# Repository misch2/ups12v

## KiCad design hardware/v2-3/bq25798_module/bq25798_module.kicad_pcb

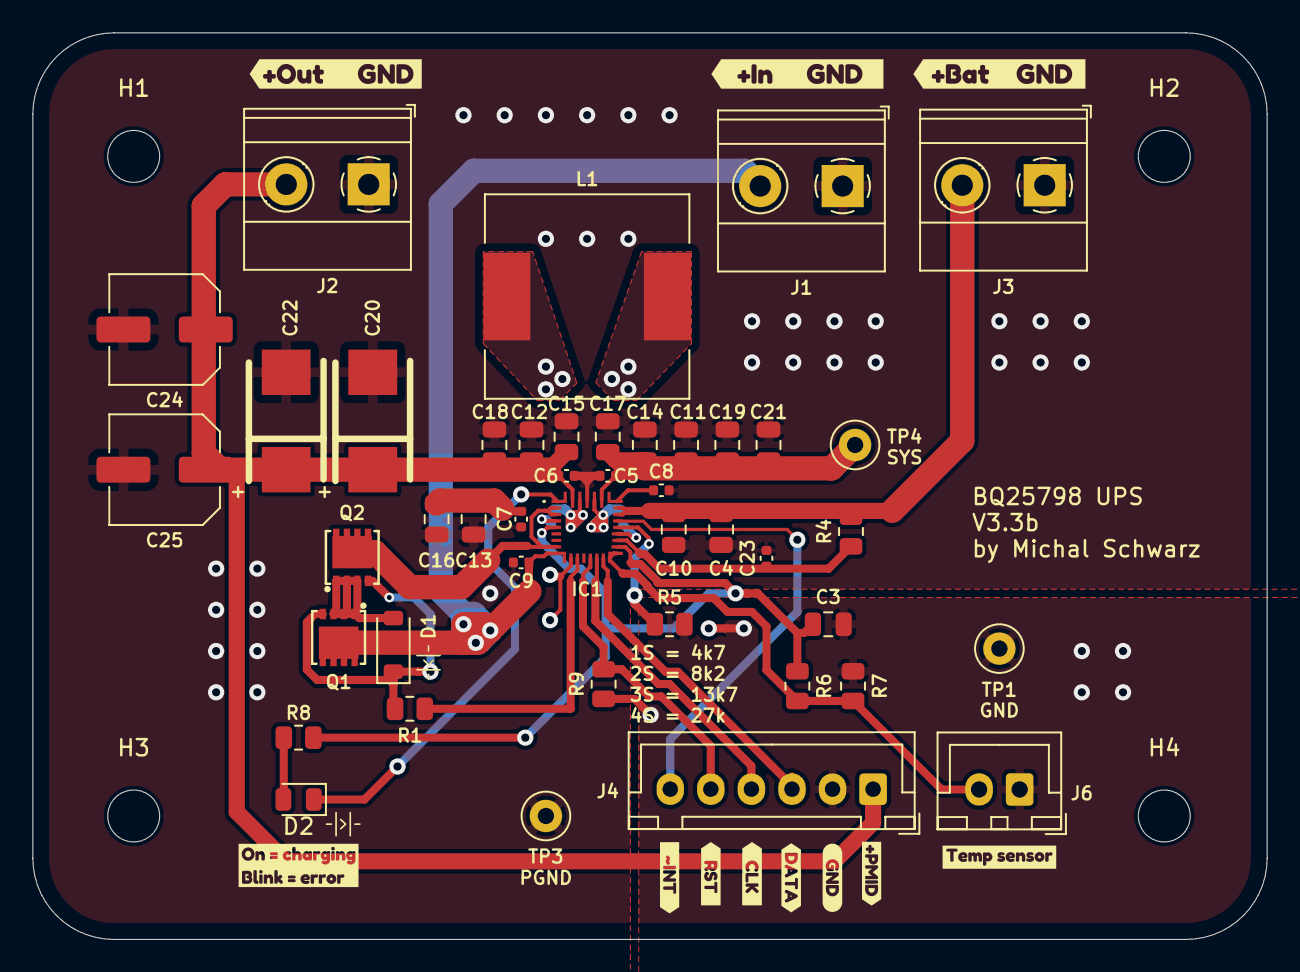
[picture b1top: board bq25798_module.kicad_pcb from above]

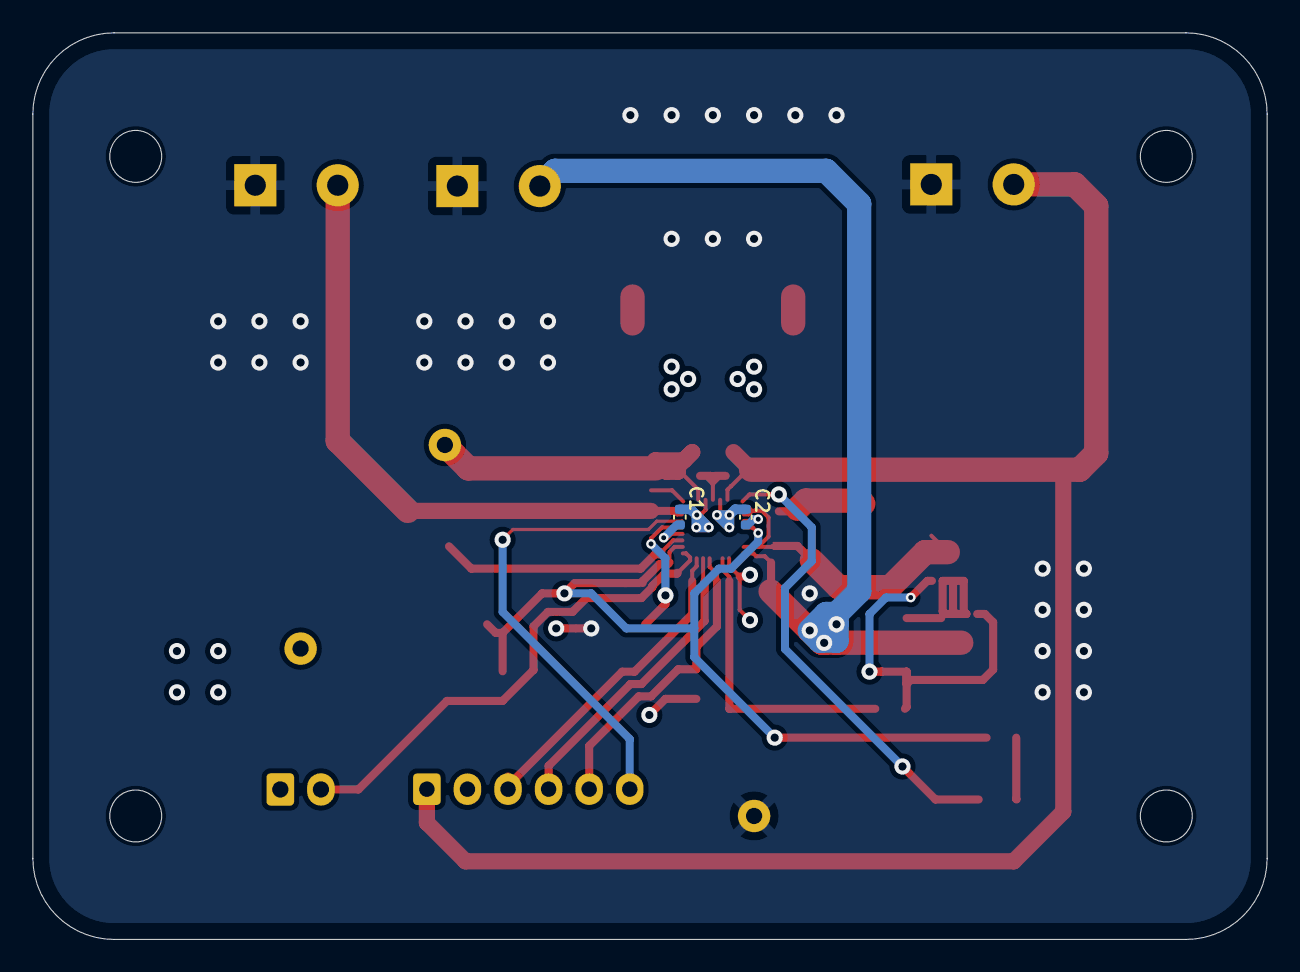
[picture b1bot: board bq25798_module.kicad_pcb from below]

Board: 4 copper layers, 76.0 x 55.9 mm, 64 parts (2 on the bottom side), 28 nets.

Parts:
C1, C2, C23: 47n 25V; C_0402_1005Metric
C3: 4.7u 10V; C_0805_2012Metric
C4, C10, C11, C12, C13, C14, C15, C16, C17, C18, C19, C21: 10u 25V; C_0805_2012Metric
C5, C6, C7, C9: 100n 25V; C_0402_1005Metric
C8: 1nF, 50V; C_0402_1005Metric
C20, C22: 47u POSCAP; CASE-D_7343
C24, C25: 47u low ESR; C_Elec_6.3x5.8
D1: 12V; D_SOD-123
D2: LED; LED_0805_2012Metric
H1, H2, H3, H4: MountingHole; MountingHole_3.2mm_M3
IC1: BQ25798RQMR; BQ25798RQMR_smaller_protected_area
J1: Input 12V DC; TerminalBlock_Phoenix_MKDS-1,5-2-5.08_1x02_P5.08mm_Horizont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
J2: Output 12V DC; TerminalBlock_Phoenix_MKDS-1,5-2-5.08_1x02_P5.08mm_Horizont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
J3: Battery; TerminalBlock_Phoenix_MKDS-1,5-2-5.08_1x02_P5.08mm_Horizont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
J4: Conn_01x06_Pin; JST_XH_B6B-XH-A_1x06_P2.50mm_Vertical
J6: NTC temp sensor; JST_XH_B2B-XH-A_1x02_P2.50mm_Vertical
L1: 2.2uH; L_12x12mm_H6mm
NT1, NT2, NT4: NetTie-2_SMD_Pad0.5mm
Q1, Q2: AON7528; DFN-8_L3.3-W3.3-P0.65-BL-3
R1: 270R; R_0805_2012Metric
R4: 100R; R_0805_2012Metric
R5: 27k 1-2%; R_0805_2012Metric
R6: 5k6; R_0805_2012Metric
R7: 33k; R_0805_2012Metric
R8: 2k2; R_0805_2012Metric
R9: 10k; R_0805_2012Metric
TP1: GND; TestPoint_Loop_D1.80mm_Drill1.0mm_Beaded
TP3: PGND; TestPoint_Loop_D1.80mm_Drill1.0mm_Beaded
TP4: SYS; TestPoint_Loop_D1.80mm_Drill1.0mm_Beaded
kibuzzard-680F50CE: G***; kibuzzard-680F50CE
kibuzzard-680F50E1: G***; kibuzzard-680F50E1
kibuzzard-680F50F5: G***; kibuzzard-680F50F5
kibuzzard-680F5553: G***; kibuzzard-680F5553
kibuzzard-680FCC32: G***; kibuzzard-680FCC32
kibuzzard-6810EFE9: G***; kibuzzard-6810EFE9
kibuzzard-6810F0BF: G***; kibuzzard-6810F0BF
kibuzzard-6810F0CD: G***; kibuzzard-6810F0CD
kibuzzard-6810F0D5: G***; kibuzzard-6810F0D5
kibuzzard-6810F062: G***; kibuzzard-6810F062
kibuzzard-68585403: G***; kibuzzard-68585403

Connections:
/I2C_SCL: IC1.14 (SCL), J4.4
/I2C_SDA: IC1.15 (SDA), J4.3
/~INT: IC1.21 (~INT), J4.6
/~RST: IC1.13 (~CE), J4.5, R9.2
BATTERY: C4.1, C10.1, IC1.22 (BAT_1), IC1.23 (BAT_2), J3.2, R4.2
BTST1: C2.1, IC1.4 (BTST1)
BTST2: C1.2, IC1.19 (BTST2)
GND: C3.2, IC1.10 (ACDRV2), J4.2, J6.1, NT1.1, R5.2, R7.1, R9.1, TP1.1
ILIM_HIZ: IC1.17 (ILIM_HIZ), NT2.1
unnamed: D1.2 (A), Q1.1 (S), Q1.2 (S), Q1.3 (S), Q2.1 (S), Q2.2 (S), Q2.3 (S)
unnamed: D1.1 (K), Q1.4 (G), Q2.4 (G), R1.2
unnamed: D2.2 (A), R8.2
unnamed: IC1.11 (ACDRV1), R1.1
unnamed: C23.1, IC1.18 (BATP), R4.1
unnamed: IC1.20 (PROG), R5.1
unnamed: IC1.2 (VBUS_1), IC1.3 (VBUS_2), IC1.8 (VAC2), NT4.1
unnamed: NT4.2, Q2.5 (D), Q2.6 (D), Q2.7 (D), Q2.8 (D), Q2.9 (D)
PGND: C4.2, C5.2, C6.2, C7.2, C8.2, C9.2, C10.2, C11.2, C12.2, C13.2, C14.2, C15.2, C16.2, C17.2, C18.2, C19.2, C20.2, C21.2, C22.2, C23.2, C24.2, C25.2, IC1.27 (GND), J1.1, J2.1, J3.1, NT1.2, TP3.1
PMID: C6.1, C12.1, C15.1, C18.1, C20.1, C22.1, C24.1, C25.1, IC1.29 (PMID), J2.2, J4.1
REGN: C3.1, IC1.5 (REGN), NT2.2, R6.1, R8.1
SDRV: C8.1, IC1.24 (SDRV_1), IC1.33 (SDRV_2)
STAT: D2.1 (K), IC1.1 (STAT_1), IC1.30 (STAT_2)
SW1: C2.2, IC1.28 (SW1), L1.2
SW2: C1.1, IC1.26 (SW2), L1.1
SYS: C5.1, C11.1, C14.1, C17.1, C19.1, C21.1, IC1.25 (SYS), TP4.1
TS: IC1.16 (TS_1), IC1.32 (TS_2), J6.2, R6.2, R7.2
VBUS: C7.1, C13.1, C16.1
VIN1: C9.1, IC1.9 (VAC1_1), IC1.31 (VAC1_2), J1.2, Q1.5 (D), Q1.6 (D), Q1.7 (D), Q1.8 (D), Q1.9 (D)

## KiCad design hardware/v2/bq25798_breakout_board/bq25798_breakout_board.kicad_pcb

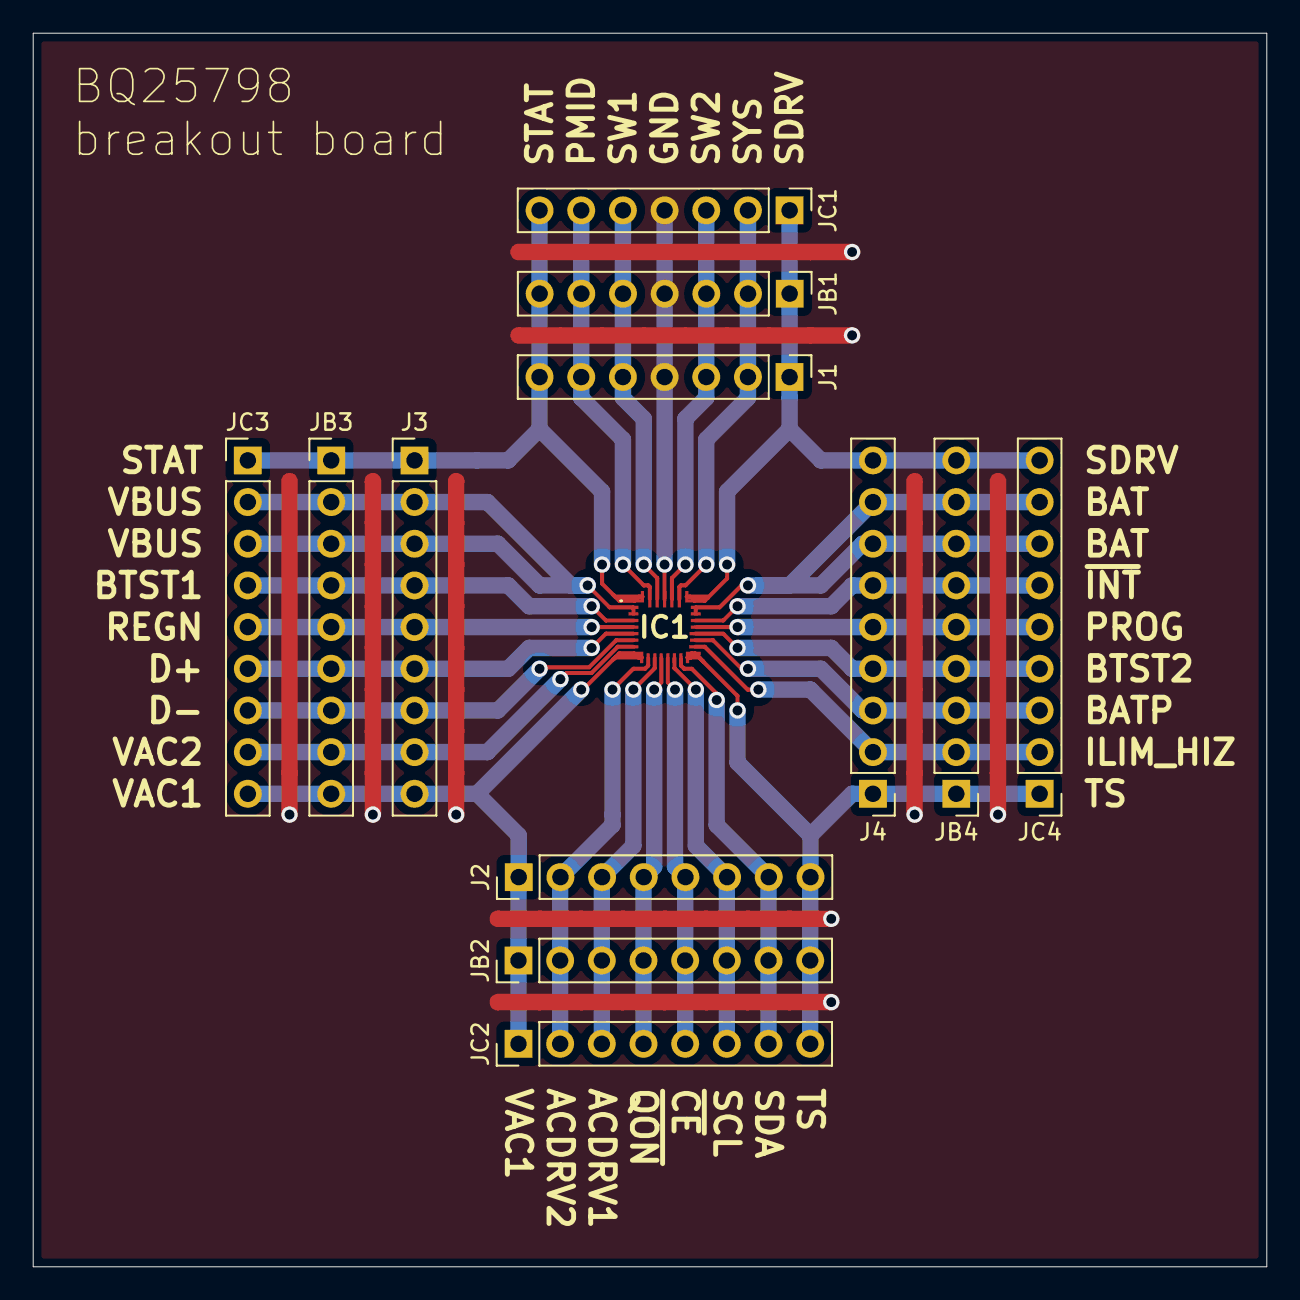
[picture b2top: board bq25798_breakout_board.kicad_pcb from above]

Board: 2 copper layers, 75.2 x 75.2 mm, 13 parts (0 on the bottom side), 27 nets.

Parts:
IC1: BQ25798RQMR
J1: Conn_01x07_Pin; PinHeader_1x07_P2.54mm_Vertical
J2: Conn_01x08_Pin; PinHeader_1x08_P2.54mm_Vertical
J3, J4: Conn_01x09_Pin; PinHeader_1x09_P2.54mm_Vertical
JB1: Conn_01x07_Pin; PinHeader_1x07_P2.54mm_Vertical
JB2: Conn_01x08_Pin; PinHeader_1x08_P2.54mm_Vertical
JB3, JB4: Conn_01x09_Pin; PinHeader_1x09_P2.54mm_Vertical
JC1: Conn_01x07_Pin; PinHeader_1x07_P2.54mm_Vertical
JC2: Conn_01x08_Pin; PinHeader_1x08_P2.54mm_Vertical
JC3, JC4: Conn_01x09_Pin; PinHeader_1x09_P2.54mm_Vertical

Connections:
unnamed: IC1.11 (ACDRV1), J2.3, JB2.3, JC2.3
unnamed: IC1.10 (ACDRV2), J2.2, JB2.2, JC2.2
unnamed: IC1.18 (BATP), J4.3, JB4.3, JC4.3
unnamed: IC1.22 (BAT_1), IC1.23 (BAT_2), J4.7, J4.8, JB4.7, JB4.8, JC4.7, JC4.8
unnamed: IC1.4 (BTST1), J3.4, JB3.4, JC3.4
unnamed: IC1.19 (BTST2), J4.4, JB4.4, JC4.4
unnamed: IC1.6 (D+), J3.6, JB3.6, JC3.6
unnamed: IC1.7 (D-), J3.7, JB3.7, JC3.7
unnamed: IC1.27 (GND), J1.4, JB1.4, JC1.4
unnamed: IC1.17 (ILIM_HIZ), J4.2, JB4.2, JC4.2
unnamed: IC1.29 (PMID), J1.6, JB1.6, JC1.6
unnamed: IC1.20 (PROG), J4.5, JB4.5, JC4.5
unnamed: IC1.5 (REGN), J3.5, JB3.5, JC3.5
unnamed: IC1.14 (SCL), J2.6, JB2.6, JC2.6
unnamed: IC1.15 (SDA), J2.7, JB2.7, JC2.7
unnamed: IC1.24 (SDRV_1), IC1.33 (SDRV_2), J1.1, J4.9, JB1.1, JB4.9, JC1.1, JC4.9
unnamed: IC1.1 (STAT_1), IC1.30 (STAT_2), J1.7, J3.1, JB1.7, JB3.1, JC1.7, JC3.1
unnamed: IC1.28 (SW1), J1.5, JB1.5, JC1.5
unnamed: IC1.26 (SW2), J1.3, JB1.3, JC1.3
unnamed: IC1.25 (SYS), J1.2, JB1.2, JC1.2
unnamed: IC1.16 (TS_1), IC1.32 (TS_2), J2.8, J4.1, JB2.8, JB4.1, JC2.8, JC4.1
unnamed: IC1.9 (VAC1_1), IC1.31 (VAC1_2), J2.1, J3.9, JB2.1, JB3.9, JC2.1, JC3.9
unnamed: IC1.8 (VAC2), J3.8, JB3.8, JC3.8
unnamed: IC1.2 (VBUS_1), IC1.3 (VBUS_2), J3.2, J3.3, JB3.2, JB3.3, JC3.2, JC3.3
unnamed: IC1.13 (~CE), J2.5, JB2.5, JC2.5
unnamed: IC1.21 (~INT), J4.6, JB4.6, JC4.6
unnamed: IC1.12 (~QON), J2.4, JB2.4, JC2.4

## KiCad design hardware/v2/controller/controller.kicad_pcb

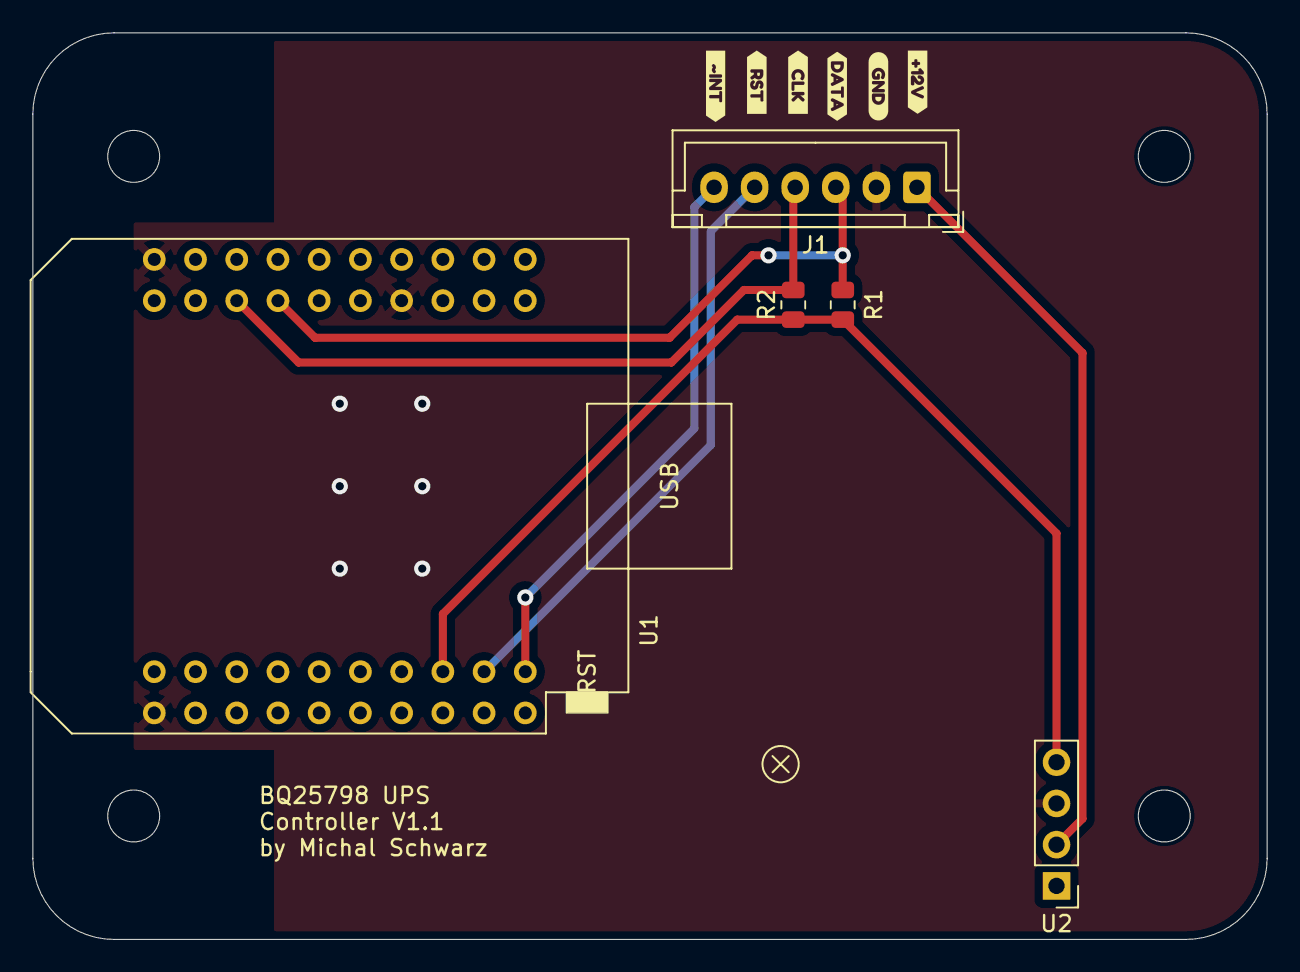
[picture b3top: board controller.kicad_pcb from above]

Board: 2 copper layers, 76.0 x 55.9 mm, 15 parts (0 on the bottom side), 7 nets.

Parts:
H1, H2, H3, H4: MountingHole; MountingHole_3.2mm_M3
J1: I2C etc.; JST_XH_B6B-XH-A_1x06_P2.50mm_Vertical
R1, R2: 2k2; R_0805_2012Metric
U1: mini_esp32 MH-ET-Live; ESP32_mini MH-ET-LIVE
U2: Micro step down converter; Micro stepdown converter
kibuzzard-683D9CD5: G***; kibuzzard-683D9CD5
kibuzzard-6810EFE9: G***; kibuzzard-6810EFE9
kibuzzard-6810F0BF: G***; kibuzzard-6810F0BF
kibuzzard-6810F0CD: G***; kibuzzard-6810F0CD
kibuzzard-6810F0D5: G***; kibuzzard-6810F0D5
kibuzzard-6810F062: G***; kibuzzard-6810F062

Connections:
3V3: R1.1, R2.1, U1.16 (3V3), U2.4 (OUT)
/I2C_SCL: J1.4, R2.2, U1.25 (IO_22/D1/SCL)
/I2C_SDA: J1.3, R1.2, U1.27 (IO_21/D2/SDA)
/PWR_IN: J1.1, U2.2 (IN)
/~INT: J1.6, U1.20 (IO_10/SD3)
/~RST: J1.5, U1.18 (IO_13/TCK)
GND: J1.2, U1.1 (GND), U1.22 (GND), U1.33 (GND), U2.3 (GND)

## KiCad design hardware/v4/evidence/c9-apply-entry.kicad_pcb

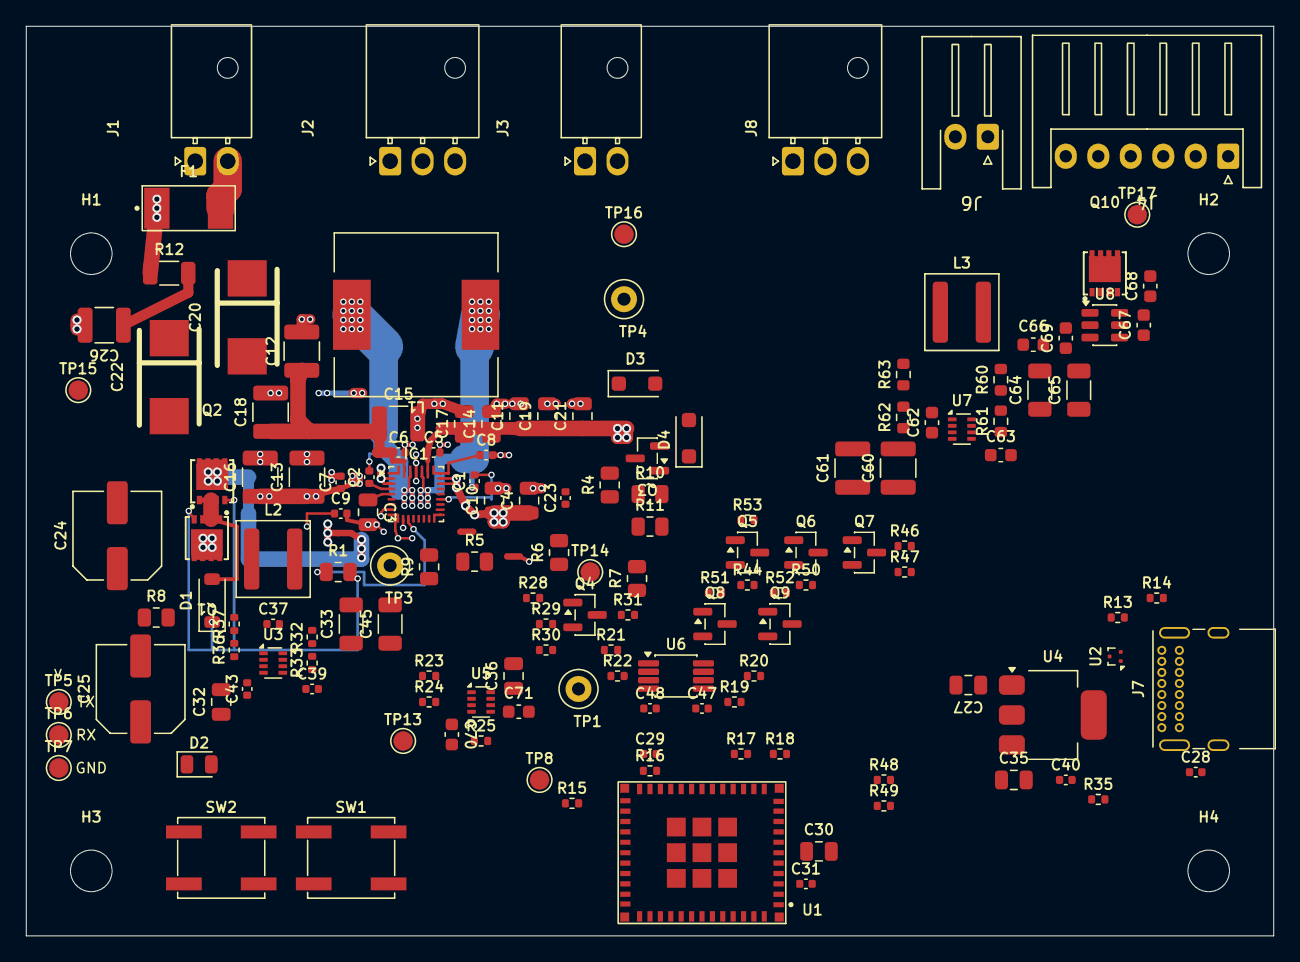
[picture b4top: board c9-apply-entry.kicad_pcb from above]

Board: 4 copper layers, 96.0 x 70.0 mm, 154 parts (0 on the bottom side), 76 nets.

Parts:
C1, C2, C23: 47n 25V; C_0402_1005Metric
C3: 4.7u 25V; C_0805_2012Metric
C4, C10, C11, C14, C17, C19, C21: 10u 25V; C_0805_2012Metric
C5: 100n 25V; C_0402_1005Metric
C6, C7, C9: 100n 50V; C_0402_1005Metric
C8: 1nF, 50V; C_0402_1005Metric
C12, C13, C15, C16, C18: 10u 50V; C_1210_3225Metric
C20, C22: 47u DNP; CASE-D_7343
C24, C25: 47u DNP; C_Elec_6.3x5.8
C26: 2.2u 100V X7R; C_1210_3225Metric
C27: 4.7u 10V USB LDO IN; C_0805_2012Metric
C28: 100n 10V USB VBUS; C_0402_1005Metric
C29: 1u RESET RC (PROVISIONAL); C_0402_1005Metric
C30: 10u MCU3V3 BULK (PROVISIONAL); C_0805_2012Metric
C31: 100n MCU3V3 HF (PROVISIONAL); C_0402_1005Metric
C32: 2.2u NORMAL IN; C_0805_2012Metric
C33, C45: 22u/35V NORMAL OUT; C_1206_3216Metric
C35: 22u USB OUT; C_0805_2012Metric
C36: 22u MCU3V3 BULK; C_0805_2012Metric
C37: 100n NORMAL BOOST; C_0402_1005Metric
C39: 33n NORMAL SS; C_0402_1005Metric
C40: 100n USB LDO OUT; C_0402_1005Metric
C43: 100n NORMAL VIN; C_0402_1005Metric
C47: 100n MCU TCA VCCB; C_0402_1005Metric
C48: 100n MAIN TCA VCCA; C_0402_1005Metric
C60, C61: 10u/50V; C_1210_3225Metric
C62, C66, C67, C68, C69: 100n/50V; C_0603_1608Metric
C63: 33n/50V; C_0603_1608Metric
C64, C65: 22u/35V; C_1206_3216Metric
C70, C71: 1u 16V X7R; C_0603_1608Metric
D1: 12V; D_SOD-123
D2: LED; LED_0805_2012Metric
D3, D4: BAS116H; D_SOD-123F
F1: 0451005.MRL 5A; Littelfuse_451_2410
H1, H2, H3, H4: MountingHole; MountingHole_3.2mm_M3
IC1: BQ25798RQMR; Texas_RQM0029A_VQFN-29_4x4mm_P0.4mm
J1: ADAPTER 4.75-21V; Molex_Nano-Fit_105313-xx02_1x02_P2.50mm_Horizontal_RevJ1
J2: VSYS OUTPUT; Molex_Nano-Fit_105313-xx03_1x03_P2.50mm_Horizontal_RevJ1
J3: BATTERY 2S/4S; Molex_Nano-Fit_105313-xx02_1x02_P2.50mm_Horizontal_RevJ1
J4: MCU / BIAS INTERFACE; JST_XH_S6B-XH-A_1x06_P2.50mm_Horizontal
J6: NTC temp sensor; JST_XH_S2B-XH-A-1_1x02_P2.50mm_Horizontal
J7: USB-C PROGRAM / NATIVE USB; USB_C_Receptacle_GCT_USB4085
J8: 5V / GND; Molex_Nano-Fit_105313-xx03_1x03_P2.50mm_Horizontal_RevJ1
L1: 2.2uH; L_12x12mm_H6mm
L2: 4.7uH XAL5030 NORMAL; L_Coilcraft_XAL5030-XXX
L3: 6.8uH; L_Coilcraft_XAL5050-XXX
NT1, NT2, NT4: NetTie-2_SMD_Pad0.5mm
Q1, Q2, Q10: AON7528; DFN-8_L3.3-W3.3-P0.65-BL-3
Q3: PMV16UN; SOT-23
Q4: BC847 INT DOMAIN ISOLATOR; SOT-23
Q5: BC857 MAIN-GATED CHG SOURCE; SOT-23
Q6: BC847 MAIN_VALID SINK; SOT-23
Q7: BC847 MCU CHG ARM SINK; SOT-23
Q8: PMV16UN MAIN_VALID; SOT-23
Q9: PMV16UN TCA_EN; SOT-23
R1: 270R; R_0805_2012Metric
R4: 100R; R_0805_2012Metric
R5: 27k 1%; R_0805_2012Metric
R6: 5k6; R_0805_2012Metric
R7: 33k; R_0805_2012Metric
R8: 2k2; R_0805_2012Metric
R9, R10: 10k; R_0805_2012Metric
R11: 4k7 SERVICE CHG_REQ SENSE DNP; R_0805_2012Metric
R12: 2R 5% pulse; R_1206_3216Metric
R13, R14: 5k1 1%; R_0402_1005Metric
R15: 10k 1% BOOT; R_0402_1005Metric
R16: 10k 1% EN; R_0402_1005Metric
R17: 10k 1% GPIO2; R_0402_1005Metric
R18: 10k 1% GPIO8; R_0402_1005Metric
R19: 4k7 MCU I2C SCL PU; R_0402_1005Metric
R20: 4k7 MCU I2C SDA PU; R_0402_1005Metric
R21: 4k7 MAIN I2C SCL PU; R_0402_1005Metric
R22: 4k7 MAIN I2C SDA PU; R_0402_1005Metric
R23: 8k2 1% MAIN_VALID DIVIDER TOP; R_0402_1005Metric
R24: 4k7 1% MAIN_VALID DIVIDER BOTTOM; R_0402_1005Metric
R25: 100k MUX ST PU; R_0402_1005Metric
R28: 10k MAIN INT PU; R_0402_1005Metric
R29: 10k INT BASE; R_0402_1005Metric
R30: 100k INT BASE PD; R_0402_1005Metric
R31: 4k7 MCU INT PU; R_0402_1005Metric
R32: 31k6 0.1% 10ppm NORMAL FB; R_0402_1005Metric
R33: 10k 0.1% NORMAL FB; R_0402_1005Metric
R35: 10k USB3V3 BLEED; R_0402_1005Metric
R36: 100k NORMAL EN; R_0402_1005Metric
R37: 38k3 NORMAL EN; R_0402_1005Metric
R44: 100k CHG BASE PU; R_0402_1005Metric
R46: 4k7 MCU CHG BASE; R_0402_1005Metric
R47: 100k MCU CHG BASE PD; R_0402_1005Metric
R48: 0R USB_DP SERIES (22R OPTION); R_0402_1005Metric
R49: 0R USB_DN SERIES (22R OPTION); R_0402_1005Metric
R50: 100k MAIN_VALID TO Q6 BASE; R_0402_1005Metric
R51: 100k NEN PU; R_0402_1005Metric
R52: 100k TCA_EN PU; R_0402_1005Metric
R53: 10k Q5 BASE LIMIT; R_0402_1005Metric
R60: 53k 0.1%; R_0603_1608Metric
R61: 10k 0.1%; R_0603_1608Metric
R62: 100k 1%; R_0603_1608Metric
R63: 38k3 1%; R_0603_1608Metric
SW1: BOOT / DOWNLOAD; SW_SPST_EVQP0
SW2: RESET; SW_SPST_EVQP0
TP1: GND; TestPoint_Loop_D1.80mm_Drill1.0mm_Beaded
TP3: PGND; TestPoint_Loop_D1.80mm_Drill1.0mm_Beaded
TP4: SYS; TestPoint_Loop_D1.80mm_Drill1.0mm_Beaded
TP5: ESP_TX (GPIO21); TestPoint_Pad_D1.5mm
TP6: ESP_RX (GPIO20); TestPoint_Pad_D1.5mm
TP7: PGND; TestPoint_Pad_D1.5mm
TP8: MCU3V3; TestPoint_Pad_D1.5mm
TP13: MAIN_3V3; TestPoint_Pad_D1.5mm
TP14: CE_N; TestPoint_Pad_D1.5mm
TP15: VIN1; TestPoint_Pad_D1.5mm
TP16: BATTERY; TestPoint_Pad_D1.5mm
TP17: F5_5V_OUT; TestPoint_Pad_D1.5mm
U1: ESP32-C3-MINI-1-N4X
U2: TPD2EUSB30A (PROVISIONAL); Texas_DRT-3
U3: TPS62933DRLR NORMAL 3V3; SOT-583-8
U4: AP7361C-33E-13 USB 3V3 LDO; SOT-223-3_TabPin2
U5: TPS2116DRL NORMAL PRIORITY; SOT-583-8
U6: TCA9517DGKR REV.D; VSSOP-8_3x3mm_P0.65mm
U7: TPS62933DRLR; SOT-583-8
U8: LM74700QDBVRQ1; SOT-23-6

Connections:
/BST_NORMAL: C37.1, U3.6 (BST)
/CHG_BASE: Q6.3 (C), R53.1
/CHG_GATE: Q3.1 (G), Q5.3 (C), R10.1
/F5_5V_OUT: C68.1, J8.3, Q10.5 (D), Q10.6 (D), Q10.7 (D), Q10.8 (D), Q10.9 (D), TP17.1 (1_1), U8.4 (CATHODE)
/F5_BST: C62.1, U7.6 (BST)
/F5_EN: R62.2, R63.1, U7.2 (EN)
/F5_FB: R60.2, R61.1, U7.8 (FB)
/F5_GATE: Q10.4 (G), U8.5 (GATE)
/F5_RAW: C64.1, C65.1, C66.1, C67.2, L3.2, Q10.1 (S), Q10.2 (S), Q10.3 (S), R60.1, U8.3 (EN), U8.6 (ANODE)
/F5_SS: C63.1, U7.7 (SS)
/F5_SW: C62.2, L3.1, U7.5 (SW)
/F5_VCAP: C67.1, U8.1 (VCAP)
/MAIN_FB: R32.2, R33.1, U3.8 (FB)
/NORMAL_EN: R36.2, R37.1, U3.2 (EN)
/NORMAL_SS: C39.1, U3.7 (SS)
/Q5_BASE_LIMITED: Q5.1 (B), R44.2, R53.2
/SW_NORMAL: C37.2, L2.1, U3.5 (SW)
ACDRV1: IC1.11 (ACDRV1), R1.1
BATP: C23.1, IC1.18 (BATP), R4.1
BATTERY: C4.1, C10.1, IC1.22 (BAT), IC1.23 (BAT), J3.2, R4.2, TP16.1 (1_1)
BTST1: C2.1, IC1.4 (BTST1)
BTST2: C1.2, IC1.19 (BTST2)
CE_BIAS: D3.1 (K), D4.1 (K), R9.2
CE_N: IC1.13 (~CE), Q3.3 (D), R9.1, TP14.1 (1_1)
CHG_AND: Q6.2 (E), Q7.3 (C)
CHG_REQ: J4.5, R11.1
GND: J6.1, NT1.1, R5.2, R7.1
I2C_SCL: IC1.14 (SCL), J4.4, R21.2, U6.2 (SCLA)
I2C_SDA: IC1.15 (SDA), J4.3, R22.2, U6.3 (SDAA)
ILIM_HIZ: IC1.17 (ILIM_HIZ), NT2.1
INT_BASE: Q4.1 (B), R29.2, R30.1
MAIN_3V3: C33.1, C45.1, C48.1, C70.1, D4.2 (A), J4.1, L2.2, Q5.2 (E), Q8.1 (G), R21.1, R22.1, R23.1, R28.1, R32.1, R44.1, R50.1, TP13.1 (1_1), U5.3 (VIN1), U5.5 (MODE), U6.1 (VCCA)
MCU3V3: C30.1, C31.1, C36.1, C47.1, R15.2, R16.2, R17.2, R18.2, R19.1, R20.1, R25.1, R31.1, R51.1, R52.1, TP8.1 (1_1), U1.3 (3V3), U5.2 (VOUT), U5.7 (VOUT), U6.8 (VCCB)
MCU_BOOT: R15.1, SW1.1, U1.23 (GPIO9)
MCU_BOOT_STRAP2: R17.1, U1.5 (GPIO2)
MCU_BOOT_STRAP8: R18.1, U1.22 (GPIO8)
MCU_CHG_ARM: R46.1, U1.12 (GPIO0)
MCU_CHG_BASE: Q7.1 (B), R46.2, R47.1
MCU_EN: C29.1, R16.1, SW2.1, U1.8 (EN)
MCU_INT: Q4.3 (C), R31.2, U1.20 (GPIO6)
MCU_SCL: R19.2, U1.19 (GPIO5), U6.7 (SCLB)
MCU_SDA: R20.2, U1.18 (GPIO4), U6.6 (SDAB)
MUX_PR1: R23.2, R24.1, U5.4 (PR1)
MUX_ST: R25.2, U5.8 (ST)
NEN: Q8.3 (D), Q9.1 (G), R51.2
unnamed: C26.1, R12.2
unnamed: D1.2 (A), Q1.1 (S), Q1.2 (S), Q1.3 (S), Q2.1 (S), Q2.2 (S), Q2.3 (S)
unnamed: D1.1 (K), Q1.4 (G), Q2.4 (G), R1.2
unnamed: D2.2 (A), R8.2
unnamed: F1.2, J1.2
unnamed: NT4.2, Q2.5 (D), Q2.6 (D), Q2.7 (D), Q2.8 (D), Q2.9 (D)
unnamed: Q6.1 (B), R50.2
unnamed: R48.1, U1.27 (USB_D+_/_GPIO19)
unnamed: R49.1, U1.26 (USB_D-_/_GPIO18)
PGND: C3.2, C4.2, C5.2, C6.2, C7.2, C8.2, C9.2, C10.2, C11.2, C12.2, C13.2, C14.2, C15.2, C16.2, C17.2, C18.2, C19.2, C20.2, C21.2, C22.2, C23.2, C24.2, C25.2, C26.2, C27.2, C28.2, C29.2, C30.2, C31.2, C32.2, C33.2, C35.2, C36.2, C39.2, C40.2, C43.2, C45.2, C47.2, C48.2, C60.2, C61.2, C63.2, C64.2, C65.2, C66.2, C68.2, C69.2, C70.2, C71.2, IC1.10 (ACDRV2), IC1.27 (GND), J1.1, J2.1 (Pin_1_1), J3.1, J4.2, J7.A1 (GND), J7.A12 (GND), J7.B1 (GND), J7.B12 (GND), J7.SH (SHIELD), J8.1 (Pin_1_1), NT1.2, Q3.2 (S), Q4.2 (E), Q7.2 (E), Q8.2 (S), Q9.2 (S), R10.2, R13.2, R14.2, R24.2, R30.2, R33.2, R35.2, R37.2, R47.2, R61.2, R63.2, SW1.2, SW2.2, TP1.1 (1_1), TP3.1 (1_1), TP7.1 (1_1), U1.1 (GND), U1.2 (GND), U1.11 (GND), U1.14 (GND), U1.36 (GND), U1.37 (GND), U1.38 (GND), U1.39 (GND), U1.40 (GND), U1.41 (GND), U1.42 (GND), U1.43 (GND), U1.44 (GND), U1.45 (GND), U1.46 (GND), U1.47 (GND), U1.48 (GND), U1.49 (GND), U1.50 (GND), U1.51 (GND), U1.52 (GND), U1.53 (GND), U2.3 (GND), U3.4 (GND), U4.2 (GND), U5.1 (GND), U6.4 (GND), U7.4 (GND), U8.2 (GND)
PMID: C6.1, C12.1, C15.1, C18.1, C20.1, C22.1, C24.1, C25.1, IC1.29 (PMID)
PROG: IC1.20 (PROG), R5.1
REGN: C3.1, D3.2 (A), IC1.5 (REGN), NT2.2, R6.1, R8.1
SDRV: C8.1, IC1.24 (SDRV)
STAT: D2.1 (K), IC1.1 (STAT)
SW1: C2.2, IC1.28 (SW1), L1.2
SW2: C1.1, IC1.26 (SW2), L1.1
SYS: C5.1, C11.1, C14.1, C17.1, C19.1, C21.1, C32.1, C43.1, C60.1, C61.1, C69.1, IC1.25 (SYS), J2.3, R36.1, R62.1, TP4.1 (1_1), U3.3 (VIN), U7.3 (VIN)
TCA_EN: Q9.3 (D), R52.2, U6.5 (EN)
TS: IC1.16 (TS), J6.2, R6.2, R7.2
UART_RX: TP6.1 (1_1), U1.30 (UART_RX_/_GPIO20)
UART_TX: TP5.1 (1_1), U1.31 (UART_TX_/_GPIO21)
USB3V3: C35.1, C40.1, C71.1, R35.1, U4.3 (VO), U5.6 (VIN2)
USB_CC1: J7.A5 (CC1), R13.1
USB_CC2: J7.B5 (CC2), R14.1
USB_DN: J7.A7 (D-), J7.B7 (D-), R49.2, U2.2 (D-)
USB_DP: J7.A6 (D+), J7.B6 (D+), R48.2, U2.1 (D+)
USB_VBUS: C27.1, C28.1, J7.A4 (VBUS), J7.A9 (VBUS), J7.B4 (VBUS), J7.B9 (VBUS), U4.1 (VI)
VBUS: C7.1, C13.1, C16.1, IC1.2 (VBUS), IC1.3 (VBUS), IC1.8 (VAC2), NT4.1
VIN1: C9.1, F1.1, IC1.9 (VAC1), Q1.5 (D), Q1.6 (D), Q1.7 (D), Q1.8 (D), Q1.9 (D), R12.1, TP15.1 (1_1)
~INT: IC1.21 (~INT), J4.6, R28.2, R29.1

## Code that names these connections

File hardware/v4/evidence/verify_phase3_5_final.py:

"""Verify exported electrical identity after presentation-only Konnect changes."""
import hashlib
import itertools
import json
from pathlib import Path
import xml.etree.ElementTree as ET

here = Path(__file__).resolve().parent
source = here.parent / 'ups_v4/ups12v_v4.kicad_sch'
def read(name):
    root = ET.parse(here / name).getroot()
    assert root.tag == 'export', 'Requires true KiCad XML, not JSON/S-expression'
    components = {}
    for c in root.findall('./components/comp'):
        components[c.get('ref')] = {
            'value': c.findtext('value'), 'footprint': c.findtext('footprint'),
            'datasheet': c.findtext('datasheet'),
            'fields': {f.get('name'): f.text for f in c.findall('./fields/field')},
            'libsource': c.find('libsource').attrib,
        }
    pins = {(p.get('ref'), p.get('pin')): n.get('name')
            for n in root.findall('./nets/net') for p in n.findall('node')}
    return components, pins

before, oldpins = read('phase3-4-usb-ldo.net.xml')
after, pins = read('phase3-5-final.net.xml')
assert before == after, 'Electrical component properties changed'
assert oldpins == pins, 'Pin-to-net mapping changed'
assert pins['IC1', '2'] == pins['IC1', '3'] == pins['C7', '1'] == pins['C13', '1'] == pins['C16', '1']
assert pins['U3', '3'] == 'SYS'
assert pins['U4', '1'] == 'USB_VBUS' and pins['U4', '3'] == 'USB3V3'
assert pins['U5', '3'] == pins['U5', '5'] == 'MAIN_3V3'
assert pins['U5', '6'] == 'USB3V3' and pins['U5', '2'] == pins['U5', '7'] == 'MCU3V3'
assert pins['Q7', '1'] == 'MCU_CHG_BASE' and pins['Q7', '2'] == 'PGND'
assert pins['Q3', '3'] == pins['R9', '1'] == pins['IC1', '13'] == 'CE_N'
assert pins['R9', '2'] == pins['D3', '1'] == pins['D4', '1'] == 'CE_BIAS'
assert pins['U6', '1'] == 'MAIN_3V3' and pins['U6', '8'] == 'MCU3V3'
erc = json.loads((here/'phase3-5-final-erc.json').read_text())
assert erc['errors'] == 0 and erc['warnings'] == 6
hashfile = lambda p: hashlib.sha256(p.read_bytes()).hexdigest()
fb = [v*(1+32200*t/10000/b)+i*32200*t
      for v,t,b,i in itertools.product([.784,.816],[.999,1.001],[.999,1.001],[-.15e-6,.15e-6])]
pr = [(v+i*(8200*t*4700*b)/(8200*t+4700*b))*(8200*t+4700*b)/(4700*b)
      for v,t,b,i in itertools.product([.92,1.08],[.99,1.01],[.99,1.01],[-.1e-6,.1e-6])]
result = {
    'status': 'PASS', 'scope': 'Saved XML identity and calculations; no hardware qualification',
    'source_sha256': hashfile(source), 'components': len(after), 'exported_pins': len(pins),
    'all_component_properties_and_all_pin_nets_preserved': True,
    'charger_F01_VBUS_connectivity': 'PASS',
    'erc_errors': erc['errors'], 'erc_warnings': erc['warnings'],
    'calculations': {
        'U3_nominal_V': .8*(1+3.22), 'U3_full_temperature_static_V': [min(fb),max(fb)],
        'U3_1A_MCU_min_before_trace_ripple_V': min(fb)-.074,
        'U3_SS_typ_ms': 33e-9*.8/5.5e-6*1000,
        'U3_EN_start_typ_V':1.21*(1+100/38.3)-.7e-6*100000,
        'U3_EN_stop_typ_V':1.17*(1+100/38.3)-2.1e-6*100000,
        'U3_EN_at_SYS18V_typ_V':18*38.3/138.3+2.1e-6*(100000*38300/138300),
        'L2_ripple_18V_500kHz_nom_A':3.376/(4.7e-6*500000)*(1-3.376/18),
        'U5_PR1_nom_at_MAIN3V3_V':3.3*4.7/12.9,
        'U5_MAIN_threshold_nom_V':12.9/4.7,
        'U5_MAIN_threshold_corners_V': [min(pr),max(pr)],
        'U4_300mA_Tj_at_50C_C':50+((5.25-3.234)*.3+5.25*80e-6)*110,
        'U4_500mA_Tj_at_50C_C':50+((5.25-3.234)*.5+5.25*80e-6)*110,
    },
    'artifact_sha256': {n:hashfile(here/n) for n in ['phase3-5-final.net.xml','phase3-5-final-erc.json','phase3-5-final.pdf','phase3-5-final.png']},
}
for n in result['artifact_sha256']:
    assert (here/n).stat().st_mtime_ns >= source.stat().st_mtime_ns, n
(here/'phase3-5-verification.json').write_text(json.dumps(result,indent=2)+'\n')
print(json.dumps(result,indent=2))

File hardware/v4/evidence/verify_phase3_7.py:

"""Read-only XML checks for the owner's minimal emergency-UART correction."""
from pathlib import Path
import csv
import hashlib
import json
import xml.etree.ElementTree as ET

HERE = Path(__file__).resolve().parent
def read(name):
    root = ET.parse(HERE / name).getroot()
    assert root.findtext('./design/tool').startswith('Eeschema 10.0.7')
    components = {c.get('ref'): c for c in root.findall('./components/comp')}
    pins = {(p.get('ref'), p.get('pin')): n.get('name')
            for n in root.findall('./nets/net') for p in n.findall('node')}
    return root, components, pins

oldroot, old, oldpins = read('phase3-6-final.net.xml')
root, new, pins = read('phase3-7-final.net.xml')
removed = {'TP9', 'TP10', 'TP11', 'TP12'}
assert set(old) - set(new) == removed and not set(new) - set(old)
expected_pins = {p: n for p, n in oldpins.items() if p[0] not in removed}
assert pins == expected_pins, 'Unexpected pin-net change/addition beyond four removed pads'
fields_allowed = {
    'TP5': {'ServiceRole'}, 'TP6': {'ServiceRole'},
    'TP7': {'ServiceRole', 'Parameters'}, 'TP8': {'ServiceRole'},
    'TP13': {'ServiceRole', 'Parameters'}, 'TP14': {'ServiceRole', 'Parameters'},
}
for ref, c in new.items():
    o = old[ref]
    for tag in ['footprint', 'datasheet', 'libsource']:
        a, b = c.find(tag), o.find(tag)
        assert (ET.tostring(a) if a is not None else None) == (ET.tostring(b) if b is not None else None), (ref, tag)
    if ref not in {'TP5', 'TP6'}:
        assert c.findtext('value') == o.findtext('value'), ref
    def fields(component):
        return {f.get('name'): f.text or '' for f in component.findall('./fields/field')}
    of, nf = fields(o), fields(c)
    for f in set(of) | set(nf):
        if f not in fields_allowed.get(ref, set()) | ({'Value'} if ref in {'TP5','TP6'} else set()):
            assert of.get(f) == nf.get(f), (ref, f)

assert new['TP5'].findtext('value') == 'ESP_TX (GPIO21)'
assert new['TP6'].findtext('value') == 'ESP_RX (GPIO20)'
assert pins['TP5','1'] == pins['U1','31'] == 'UART_TX'
assert pins['TP6','1'] == pins['U1','30'] == 'UART_RX'
assert pins['TP7','1'] == 'PGND'
for pin, token in [('31','GPIO21'),('30','GPIO20')]:
    node = next(n for n in root.findall('./nets/net/node') if n.get('ref') == 'U1' and n.get('pin') == pin)
    assert token in node.get('pinfunction','')
for net, refs in [('UART_TX', {'TP5','U1'}), ('UART_RX', {'TP6','U1'})]:
    assert {r for (r,p),n in pins.items() if n == net} == refs, net
assert pins['TP8','1'] == 'MCU3V3' and pins['TP13','1'] == 'MAIN_3V3'
for ref in ['TP5','TP6','TP7','TP8','TP13','TP14','TP15','TP16','TP17']:
    assert new[ref].findtext('footprint') == 'TestPoint:TestPoint_Pad_D1.5mm'
switches = [r for r,c in new.items() if c.find('libsource').get('lib') == 'Switch']
assert switches, 'Expected existing BOOT/RESET buttons'
for net in ['MCU_EN','MCU_BOOT']:
    assert any(r in switches and n == net for (r,p),n in pins.items()), net
f5 = {'U7','U8','Q10','L3','J8'} | {f'R{i}' for i in range(60,64)} | {f'C{i}' for i in range(60,70)}
assert len(f5) == 19
f5nets = {n for (r,p),n in pins.items() if r in f5}
base_nets = {n for (r,p),n in pins.items() if r not in f5 | {'TP17'}}
assert f5nets & base_nets == {'SYS','PGND'}
assert {r for (r,p),n in pins.items() if n == 'F5_5V_OUT'} <= f5 | {'TP17'}
erc = json.loads((HERE / 'phase3-7-final-erc.json').read_text())
assert (erc['errors'],erc['warnings']) == (0,4)
assert {v['description'] for v in erc['violations']} == {
    v['description'] for v in json.loads((HERE / 'phase3-6-final-erc.json').read_text())['violations']}
sha = lambda p: hashlib.sha256(p.read_bytes()).hexdigest()
assert sha(HERE / 'phase3-7-entry.kicad_sch') == json.loads((HERE / 'phase3-6-verification.json').read_text())['source_sha256']
report = {
    'status': 'PASS: minimal UART correction; no hardware validation',
    'source_sha256': sha(HERE.parent / 'ups_v4/ups12v_v4.kicad_sch'),
    'components': len(new), 'retained_pin_entries_verified': len(pins),
    'removed': sorted(removed), 'all_remaining_pin_nets_preserved': True,
    'all_power_USB_F5_and_button_properties_preserved': True,
    'uart': {'TP5': 'U1.31 GPIO21 TX', 'TP6': 'U1.30 GPIO20 RX', 'TP7': 'PGND'},
    'separate_voltage_measurements': {'TP8':'MCU3V3','TP13':'MAIN_3V3'},
    'F0_F5_parts': sorted(f5), 'ERC': [erc['errors'],erc['warnings']],
    'PCB_DRC_parity': 'Not applicable: no V4 PCB; mandatory before release',
    'artifact_sha256': {name: sha(HERE / name) for name in [
        'phase3-7-final.net.xml','phase3-7-final-erc.json','phase3-7-final.pdf','phase3-7-final.png']},
}
(HERE / 'phase3-7-verification.json').write_text(json.dumps(report,indent=2)+'\n',encoding='utf-8')
with (HERE / 'phase3-7-population.csv').open('w',newline='',encoding='utf-8') as f:
    writer = csv.writer(f)
    writer.writerow(['Reference','Value','F0_fitted','F5_fitted','Copper_only'])
    for r in sorted(f5 | {r for r in new if r.startswith('TP')}):
        copper = r.startswith('TP')
        writer.writerow([r,new[r].findtext('value'),0,0 if copper else 1,'yes' if copper else 'no'])
print(json.dumps({k: report[k] for k in ['status','components','retained_pin_entries_verified','removed','ERC']}))

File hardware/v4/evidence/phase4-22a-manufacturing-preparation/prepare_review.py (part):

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                                       loss2A125_mW=resistance * 4000 * hot,
                                       conditional_J8_low_V=(4.81714 - resistance * 2 * hot) if name.startswith('F5 RAW') else None))
    sheet = []
    for label, width, current in [('SYS/BATTERY trunk', 3, 3.74), ('VIN1/VBUS distribution', 2.2, 3.3),
                                  ('F5 OUT trunk', 2, 2), ('F5 SYS branch', 1.5, 2)]:
        for t in (35, 30.5, 17.5, 15.2):
            r = rho * .01 / (width * 1e-3 * t * 1e-6)
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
